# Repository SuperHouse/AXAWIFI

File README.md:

AXA Electric Window Motor WiFi Controller (ESP8266)
===================================================
Copyright 2017-2021 SuperHouse Automation Pty Ltd  www.superhouse.tv  

An add-in board for AXA domestic electric window mechanisms, to fit
into the battery compartment in place of the AA cells that are normally
installed. It uses an ESP8266 to connect to WiFi, and can then send
control signals to the AXA window motor using LINbus.

An external 12Vdc power connection is required. Power is supplied to
the Axa Wifi board, which in turn passes on power and data to the
existing controller in the window motor.

Features:

 * ESP8266 microcontroller with WiFi.
 * LIN bus interface.
 * Fits inside Axa battery compartment.

More information:

  [www.superhouse.tv/axawifi](https://www.superhouse.tv/axawifi)

INSTALLATION
------------
The design is saved as an EAGLE project. Install EAGLE and open the
files directly.

CREDITS
-------
Designed by Jonathan Oxer jon@oxer.com.au

DISTRIBUTION
------------
The specific terms of distribution of this project are governed by the
license referenced below.

LICENSE
-------
Licensed under the TAPR Open Hardware License (www.tapr.org/OHL).
The "license" folder within this repository also contains a copy of
this license in plain text format.

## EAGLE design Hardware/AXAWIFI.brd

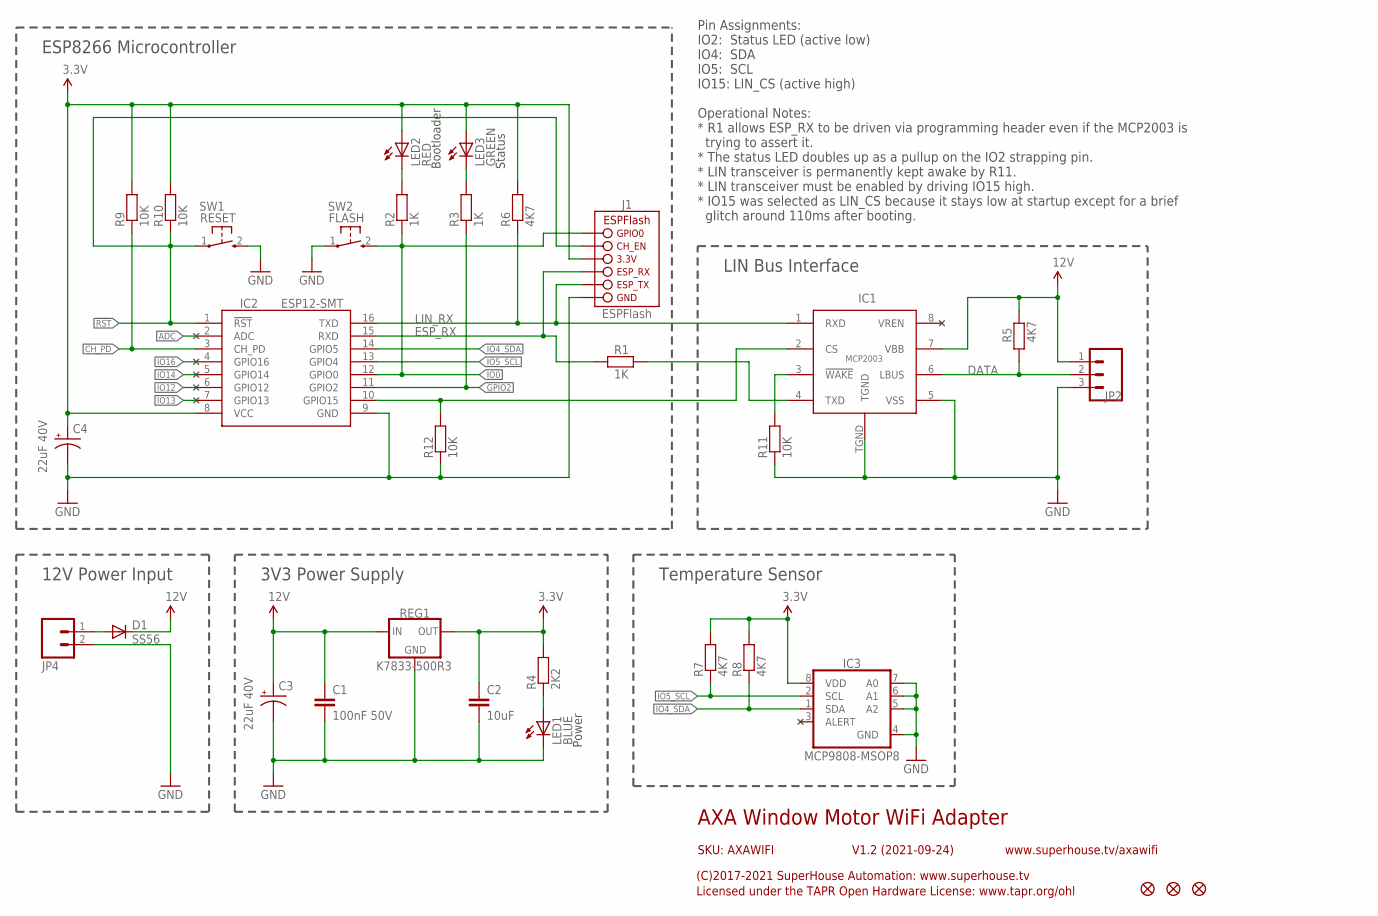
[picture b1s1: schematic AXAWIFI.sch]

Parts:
C1: 100nF 50V; C0603
C2: 10uF; C0805
C3, C4: 22uF 40V; PANASONIC_C
D1: SS56; SMA-DIODE
FID1, FID2, FID3: FIDUCIAL1X2.5; FIDUCIAL-1X2.5
IC1: MCP2003; SOIC8T
IC2: ESP12-SMT; ESP12
IC3: MCP9808-MSOP8; MSOP-8
J1: ESPFLASH-1X6-2.54-SOCKET; 1X6-2.54-SOCKET
JP2: M03-PLAIN; 1X03
JP4: M02-SCREW-3.5MM; SCREWTERMINAL-3.5MM-2
LED1: BLUE; LED-0603
LED2: RED; LED-0603
LED3: GREEN; LED-0603
R1, R2, R3: 1K; R0603
R4: 2K2; R0603
R5, R6, R7, R8: 4K7; R0603
R9, R10, R11, R12: 10K; R0603
REG1: K7833-500R3; K78XX-500R3
SW1: RESET; TACTILE_SMT_3X4X2
SW2: FLASH; TACTILE_SMT_3X4X2

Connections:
3.3V: C2.1, C4.+, IC2.8 (VCC), IC3.8 (VDD), J1.4 (3.3V), LED2.A, LED3.A, R4.2, R6.2, R7.2, R8.2, R9.2, R10.2, REG1.3 (OUT)
12V: C1.1, C3.+, D1.C, IC1.7 (VBB), JP2.1, R5.2, REG1.1 (IN)
!LIN_WAKE: IC1.3 (!WAKE), R11.2
!RST: IC2.1 (!RST), J1.5 (CH_EN), R10.1, SW1.1
ADC: IC2.2 (ADC)
CH_PD: IC2.3 (CH_PD), R9.1
DATA: IC1.6 (LBUS), JP2.2, R5.1
ESP_RX: IC2.15 (RXD), J1.3 (ESP_RX), R1.1
GND: C1.2, C2.2, C3.-, C4.-, IC1.5 (VSS), IC1.TGND, IC2.9 (GND), IC3.4 (GND), IC3.5 (A2), IC3.6 (A1), IC3.7 (A0), J1.1 (GND), JP2.3, JP4.2, LED1.C, R11.1, R12.1, REG1.2 (GND), SW1.2 (S), SW2.1
GPIO2: IC2.11 (GPIO2), R3.1
GPIO15: IC1.2 (CS), IC2.10 (GPIO15), R12.2
IO0: IC2.12 (GPIO0), J1.6 (GPIO0), R2.1, SW2.2 (S)
IO4_SDA: IC2.14 (GPIO5), IC3.1 (SDA), R8.1
IO5_SCL: IC2.13 (GPIO4), IC3.2 (SCL), R7.1
IO12: IC2.6 (GPIO12)
IO13: IC2.7 (GPIO13)
IO14: IC2.5 (GPIO14)
IO16: IC2.4 (GPIO16)
LIN_RX: IC1.1 (RXD), IC2.16 (TXD), J1.2 (ESP_TX), R6.1
unnamed: D1.A, JP4.1
unnamed: IC1.4 (TXD), R1.2
unnamed: LED3.C, R3.2
unnamed: LED1.A, R4.1
unnamed: LED2.C, R2.2

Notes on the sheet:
AXA Window Motor WiFi Adapter
Power
3V3 Power Supply
SKU: AXAWIFI
(C)2017-2021 SuperHouse Automation: www.superhouse.tv
Licensed under the TAPR Open Hardware License: www.tapr.org/ohl
www.superhouse.tv/axawifi
V1.2 (2021-09-24)
12V Power Input
ESP8266 Microcontroller
LIN Bus Interface
Pin Assignments: IO2: Status LED (active low) IO4: SDA IO5: SCL IO15: LIN_CS (active high) Operational Notes: * R1 allows ESP_RX to be driven via programming header even if the MCP2003 is trying to assert it. * The status LED doubles up as a pullup on the IO2 strapping pin. * LIN transceiver is per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
Temperature Sensor
Bootloader
Status

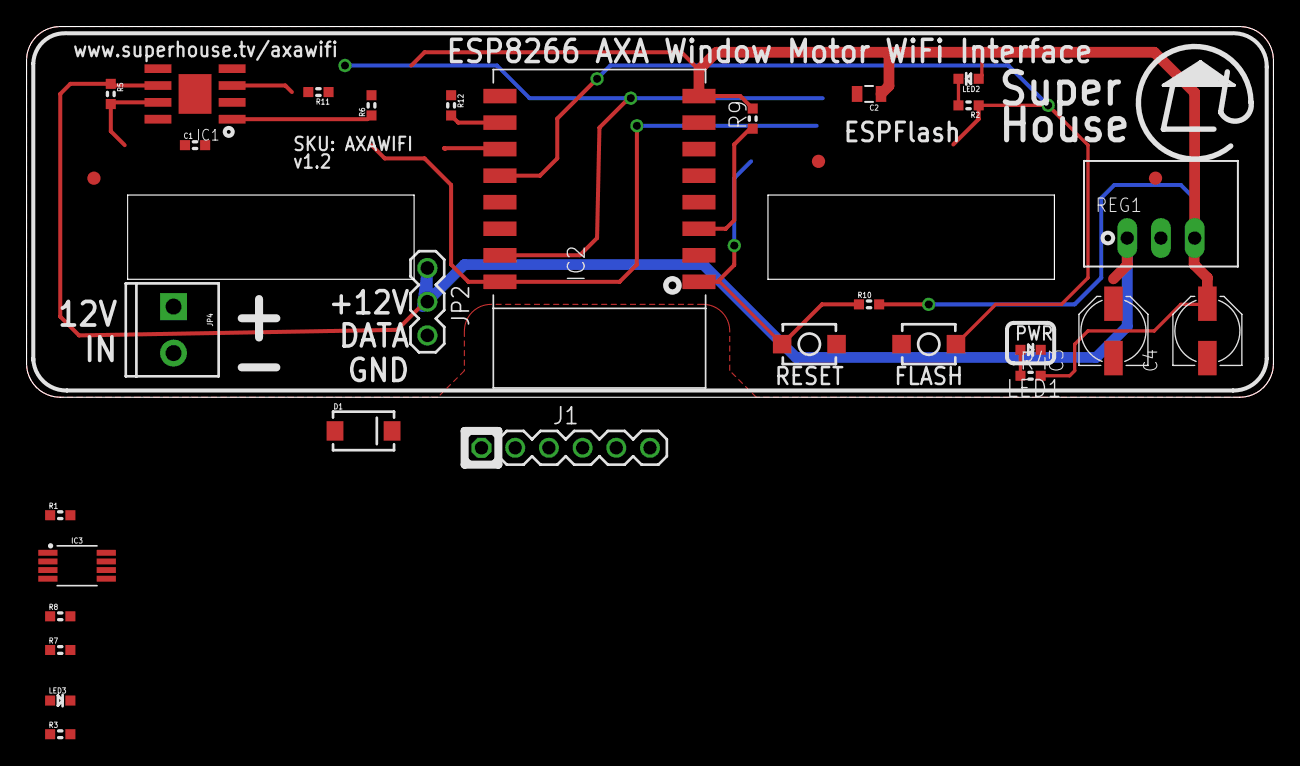
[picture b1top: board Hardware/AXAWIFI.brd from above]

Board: 2 copper layers, 94.0 x 27.9 mm, 32 parts (0 on the bottom side), 19 nets.

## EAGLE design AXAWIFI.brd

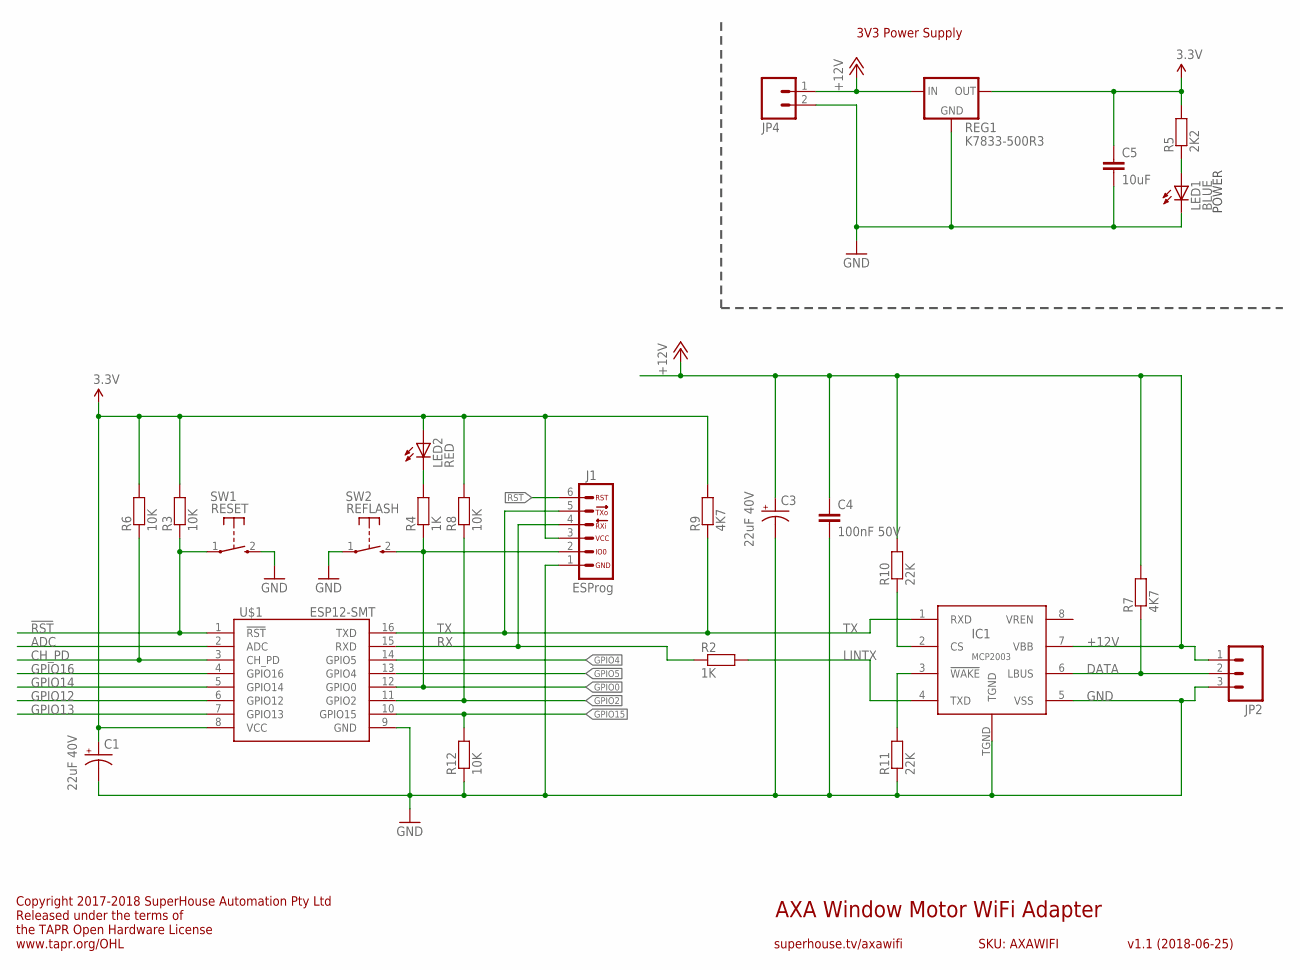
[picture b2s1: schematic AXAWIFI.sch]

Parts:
C1, C3: 22uF 40V; UD-6,3X5,8_NICHICON
C4: 100nF 50V; C0603
C5: 10uF; C0805
IC1: MCP2003; SOIC8T
J1: ESPROG-SOCKET; ESPROG-S
JP2: M03PTH; 1X03
JP4: M02-SCREW-3.5MM; SCREWTERMINAL-3.5MM-2
LED1: BLUE; LED-0603
LED2: RED; LED-0603
R2, R4: 1K; R0603
R3, R6, R8, R12: 10K; R0603
R5: 2K2; R0603
R7, R9: 4K7; R0603
R10, R11: 22K; R0603
REG1: K7833-500R3; K78XX-500R3
SW1: RESET; TACTILE_SMT_3X4X2
SW2: REFLASH; TACTILE_SMT_3X4X2
U$1: ESP12-SMT; ESP12

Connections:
3.3V: C1.+, C5.1, J1.3, LED2.A, R3.2, R5.2, R6.2, R8.2, R9.2, REG1.3 (OUT), U$1.8 (VCC)
!RST: J1.6, R3.1, SW1.1, U$1.1 (!RST)
+12V: C3.+, C4.1, IC1.7 (VBB), JP2.1, JP4.1, R7.2, R10.2, REG1.1 (IN)
ADC: U$1.2 (ADC)
CH_PD: R6.1, U$1.3 (CH_PD)
DATA: IC1.6 (LBUS), JP2.2, R7.1
GND: C1.-, C3.-, C4.2, C5.2, IC1.5 (VSS), IC1.TGND, J1.1, JP2.3, JP4.2, LED1.C, R11.1, R12.1, REG1.2 (GND), SW1.2 (S), SW2.1, U$1.9 (GND)
GPIO0: J1.2, R4.1, SW2.2 (S), U$1.12 (GPIO0)
GPIO2: R8.1, U$1.11 (GPIO2)
GPIO4: U$1.14 (GPIO5)
GPIO5: U$1.13 (GPIO4)
GPIO12: U$1.6 (GPIO12)
GPIO13: U$1.7 (GPIO13)
GPIO14: U$1.5 (GPIO14)
GPIO15: R12.2, U$1.10 (GPIO15)
GPIO16: U$1.4 (GPIO16)
LINTX: IC1.4 (TXD), R2.2
unnamed: IC1.2 (CS), R10.1
unnamed: IC1.3 (!WAKE), R11.2
unnamed: LED1.A, R5.1
unnamed: LED2.C, R4.2
RX: J1.4, R2.1, U$1.15 (RXD)
TX: IC1.1 (RXD), J1.5, R9.1, U$1.16 (TXD)

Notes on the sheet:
AXA Window Motor WiFi Adapter
v1.1 (2018-06-25)
superhouse.tv/axawifi
SKU: AXAWIFI
Copyright 2017-2018 SuperHouse Automation Pty Ltd Released under the terms of the TAPR Open Hardware License www.tapr.org/OHL
POWER
3V3 Power Supply

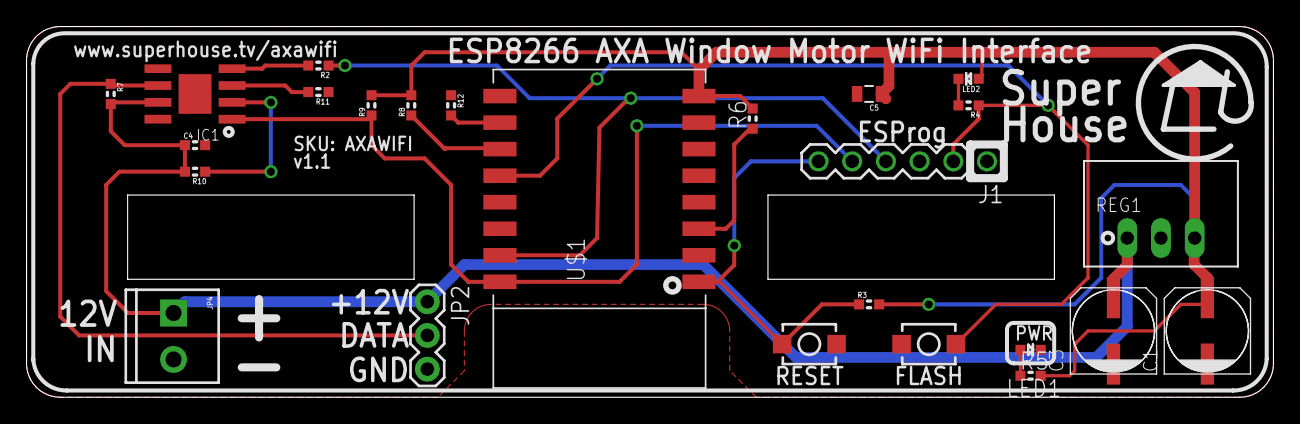
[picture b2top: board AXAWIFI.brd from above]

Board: 2 copper layers, 94.0 x 27.9 mm, 25 parts (0 on the bottom side), 16 nets.

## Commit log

2018-03-22 Initial import of project from June 2017
2018-06-25 Replaced voltage regulator module with K7833 for v1.1 release
2019-04-15 Improved clearances
2019-09-10 Replaced parts using SuperHouse library
2019-09-10 Replaced programming header with ESProg header
2020-05-27 Replace parts using SuperHouse library for 3D models
2021-09-24 Rearranged project files into more logical structure.
2021-09-24 Added images of prototype test fits.
2021-09-24 Replaced obsolete programming header with ESPFlash header. Set MCP2003 to be permanently awake. Set MCP2003 to be deselected unless explicitly selected. Major restructure of schematic. Replaced parts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
2021-09-24 Assigned IO15 as LIN_CS.
2021-09-24 Rationalised part values and reordered designators.

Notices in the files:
AXAWIFI.brd:
(c) 2018 SuperHouse Automation Pty Ltd
Open Hardware License
